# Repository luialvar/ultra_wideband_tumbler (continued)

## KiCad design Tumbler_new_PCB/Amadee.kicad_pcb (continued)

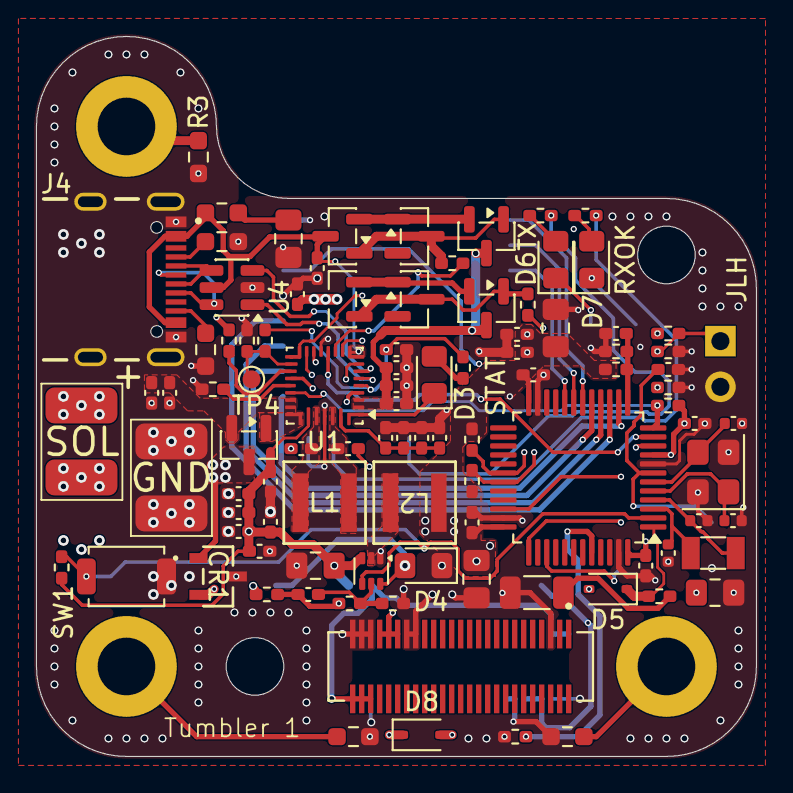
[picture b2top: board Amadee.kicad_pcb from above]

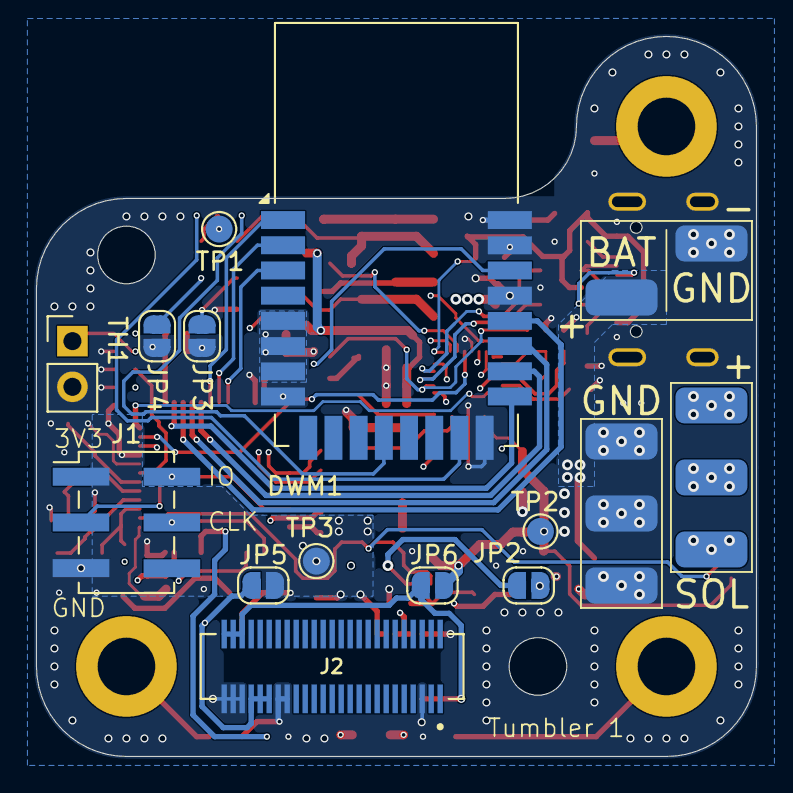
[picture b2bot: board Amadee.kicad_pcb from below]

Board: 4 copper layers, 40.0 x 40.0 mm, 123 parts (20 on the bottom side), 74 nets.

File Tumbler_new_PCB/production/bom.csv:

Designator,Footprint,Quantity,Value,LCSC Part #
"C1, C15, C2, C28, C31, C33, C34, C35, C38, C5, C9",0402,11,100nF,
"C10, C11, C12, C13, C14, C16, C17, C18, C19, C20, C3, C37, C4",0402,13,10uF,
C21,0805,1,4.7uF X7R,
"C22, C36",0402,2,47pF,
"C23, C24",0805,2,22uF X7R,
"C25, C26",0402,2,15pF,
C27,1206,1,100uF,
C29,0805,1,4.7uF,
"C30, C32",0402,2,10pF,
C39,0805,1,2.2uF,
"C6, C7",0402,2,47nF,
C8,0402,1,4.7uF 10V,
CR1,CR_SOT-23_PTD,1,PSM712-LF-T7,C32677
"D1, D2",SOT-23,2,BZX84C10A,C5155278
"D3, D4, D6, D7",0805,4,LED 0805,C2296
"D5, D8",D_SOD-323,2,1N5819WS,
DWM1,DWM1000,1,DWM3000,C42419011
J2,HRS_DF12NC-50DS-0.5V_51_,1,DF12NC-50DS-0.5V_51_,C3647189
J3,HRS_DF12NC_5.0_-50DP-0.5V_51_,1,DF12NC_5.0_-50DP-0.5V_51_,C3644230
J4,GCT_USB4105-GF-A-120,1,USB4105-GF-A-120,C5184243
"L1, L2",IND_XGL4020_COC,2,XGL4020-222MEC,
"P1, P10, P11, P12, P2, P3, P4, P5, P6, P7, P8, P9",SolderPad_4mm_2mm,12,SolderPad_4mm_2mm,
"Q1, Q2, Q3, Q4, Q5",SOT-23,5,AO3400A,C20917
"R1, R2, R3",0603,3,1M,
R10,0402,1,5.23k,
R11,0402,1,30.1k,
"R12, R17",0402,2,100R,
R13,0402,1,2k2,
R14,0402,1,450k,
"R15, R25",0402,2,100k,
"R16, R24, R26",0402,3,510R,
"R18, R21, R22, R23",0402,4,10k,
"R19, R20, R4",0402,3,1M,
"R27, R28",0603,2,5.1k,
R29,0603,1,2.2R,
"R5, R6",0402,2,300R,
R7,0402,1,320k,
R8,0402,1,680k,
R9,0402,1,4.7k 1%-2%,
SW1,SW_SPST_TS-1088-xR020,1,SW_Push,C720477
"TP1, TP2, TP3",TestPoint_Pad_D1.5mm,3,TestPoint,
TP4,TestPoint_Pad_D1.0mm,1,TestPoint,
U1,Texas_RQM0029A_VQFN-29_4x4mm_P0.4mm,1,BQ25798,
U2,SOT-563,1,TPS62A056x,
U3,LQFP-48_7x7mm_P0.5mm,1,STM32L431CCT6,C486681
U4,SOT-23-6,1,WE-TVS-82400102,
Y1,Crystal_SMD_3215-2Pin_3.2x1.5mm,1,32.768kHz Q13FC13500004,C32346
Y2,Crystal_SMD_3225-4Pin_3.2x2.5mm,1,16MHz X322516MLB4SI,C13738

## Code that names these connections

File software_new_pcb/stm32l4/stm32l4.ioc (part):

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Mcu.Name=STM32L431C(B-C)Tx
Mcu.Package=LQFP48
Mcu.UserName=STM32L431CCTx
PA0.GPIOParameters=GPIO_Label
PA0.GPIO_Label=DWM_IRQ
PA0.Signal=GPXTI0
PA1.GPIOParameters=GPIO_Label
PA1.GPIO_Label=BMS_QONn
PA1.Signal=GPIO_Output
PA10.GPIOParameters=GPIO_Label
PA10.GPIO_Label=BMS_SDA
PA10.Mode=I2C
PA10.Signal=I2C1_SDA
PA13\ (JTMS-SWDIO).Mode=Trace_Asynchronous_SW
PA13\ (JTMS-SWDIO).Signal=SYS_JTMS-SWDIO
PA14\ (JTCK-SWCLK).Mode=Trace_Asynchronous_SW
PA14\ (JTCK-SWCLK).Signal=SYS_JTCK-SWCLK
PA2.GPIOParameters=GPIO_Label
PA2.GPIO_Label=BMS_INT
PA2.Signal=GPIO_Input
PA3.Signal=ADCx_IN8
PA4.GPIOParameters=GPIO_Speed,GPIO_PuPd,GPIO_Label
PA4.GPIO_Label=SPI1_NSS
PA4.GPIO_PuPd=GPIO_PULLUP
PA4.GPIO_Speed=GPIO_SPEED_FREQ_MEDIUM
PA4.Signal=GPIO_Output
PA5.Mode=Full_Duplex_Master
PA5.Signal=SPI1_SCK
PA6.Mode=Full_Duplex_Master
PA6.Signal=SPI1_MISO
PA7.Mode=Full_Duplex_Master
PA7.Signal=SPI1_MOSI
PA9.GPIOParameters=GPIO_Label
PA9.GPIO_Label=BMS_SCL
PA9.Mode=I2C
PA9.Signal=I2C1_SCL
PB0.GPIOParameters=GPIO_Label
PB0.GPIO_Label=EXTON
PB0.Signal=GPIO_Output
PB1.GPIOParameters=GPIO_Speed,GPIO_Label
PB1.GPIO_Label=WAKEUP
PB1.GPIO_Speed=GPIO_SPEED_FREQ_MEDIUM
PB1.Signal=GPIO_Output
PB2.GPIOParameters=PinState,GPIO_Label
PB2.GPIO_Label=DWM_nRST
PB2.PinState=GPIO_PIN_SET
PB2.Signal=GPIO_Output
PB3\ (JTDO-TRACESWO).Mode=Trace_Asynchronous_SW
PB3\ (JTDO-TRACESWO).Signal=SYS_JTDO-SWO
PC13.GPIOParameters=GPIO_Label
PC13.GPIO_Label=Buck_EN
PC13.Signal=GPIO_Output
PC14-OSC32_IN\ (PC14).Mode=LSE-External-Oscillator
PC14-OSC32_IN\ (PC14).Signal=RCC_OSC32_IN
PC15-OSC32_OUT\ (PC15).Mode=LSE-External-Oscillator
PC15-OSC32_OUT\ (PC15).Signal=RCC_OSC32_OUT
PH0-OSC_IN\ (PH0).Mode=HSE-External-Oscillator
PH0-OSC_IN\ (PH0).Signal=RCC_OSC_IN
PH1-OSC_OUT\ (PH1).Mode=HSE-External-Oscillator
PH1-OSC_OUT\ (PH1).Signal=RCC_OSC_OUT
RCC.HSE_VALUE=8000000
RCC.SYSCLKFreq_VALUE=80000000
RCC.SYSCLKSource=RCC_SYSCLKSOURCE_PLLCLK
board=custom
